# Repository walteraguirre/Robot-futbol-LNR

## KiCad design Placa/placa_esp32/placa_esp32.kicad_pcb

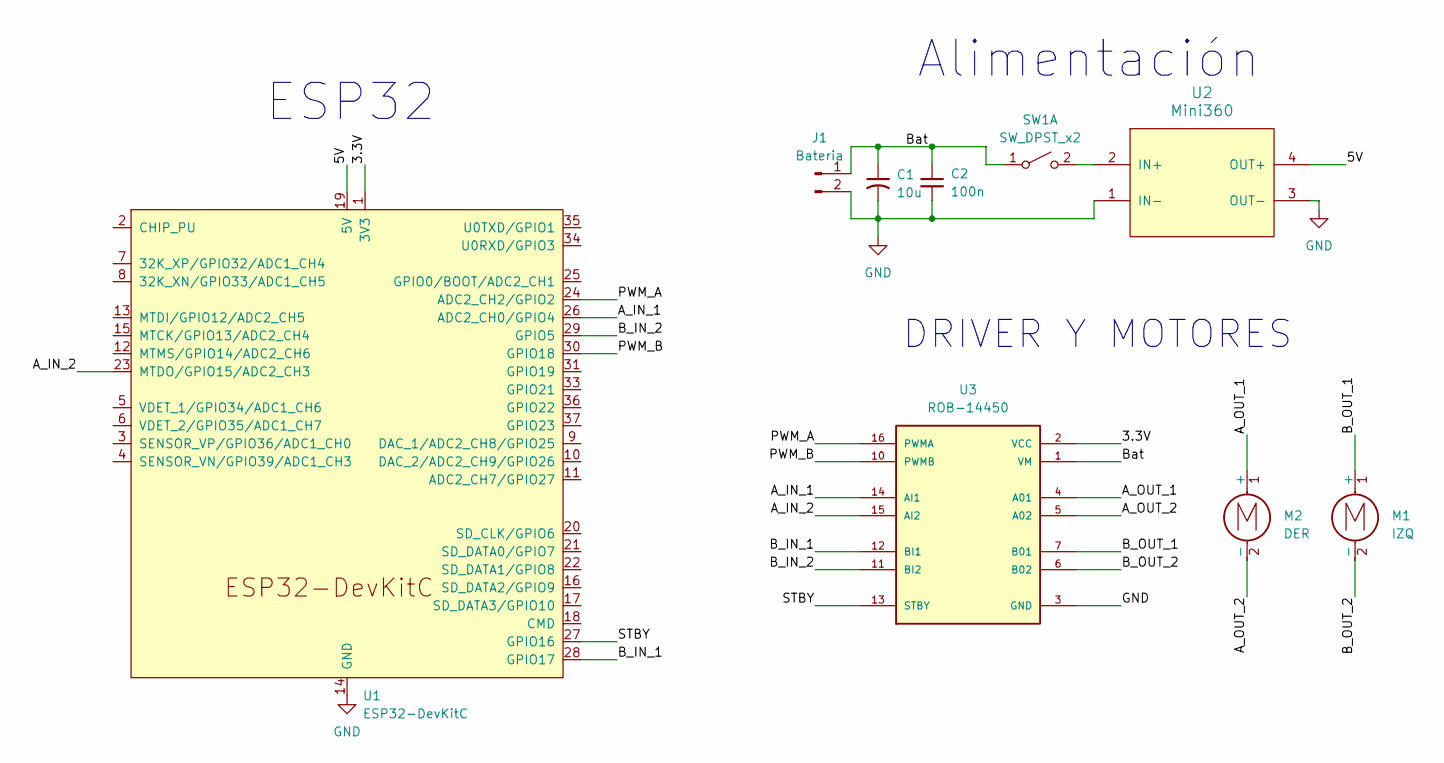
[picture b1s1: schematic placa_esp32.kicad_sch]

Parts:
C1: 10u; C_Radial_D10.0mm_H12.5mm_P5.00mm
C2: 100n; C_Disc_D10.0mm_W2.5mm_P5.00mm
J1: Bateria; JST_EH_B2B-EH-A_1x02_P2.50mm_Vertical
M1: IZQ; JST_EH_B2B-EH-A_1x02_P2.50mm_Vertical
M2: DER; JST_EH_B2B-EH-A_1x02_P2.50mm_Vertical
SW1: SW_DPST_x2; JST_EH_B2B-EH-A_1x02_P2.50mm_Vertical
U1: ESP32-DevKitC
U2: Mini360; Mini360_step-down
U3: ROB-14450; MODULE_ROB-14450; PARTREV 11-13-17

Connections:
/3.3V: U1.1 (3V3), U3.2 (VCC)
/5V: U1.19 (5V), U2.4 (OUT+)
/A_IN_1: U1.26 (ADC2_CH0/GPIO4), U3.14 (AI1)
/A_IN_2: U1.23 (MTDO/GPIO15/ADC2_CH3), U3.15 (AI2)
/A_OUT_1: M2.1 (+), U3.4 (A01)
/A_OUT_2: M2.2 (-), U3.5 (A02)
/B_IN_1: U1.28 (GPIO17), U3.12 (BI1)
/B_IN_2: U1.29 (GPIO5), U3.11 (BI2)
/B_OUT_1: M1.1 (+), U3.7 (B01)
/B_OUT_2: M1.2 (-), U3.6 (B02)
/Bat: C1.1, C2.1, J1.1, SW1.1 (A), U3.1 (VM)
/PWM_A: U1.24 (ADC2_CH2/GPIO2), U3.16 (PWMA)
/PWM_B: U1.30 (GPIO18), U3.10 (PWMB)
/STBY: U1.27 (GPIO16), U3.13 (STBY)
GND: C1.2, C2.2, J1.2, U1.14 (GND), U1.32 (GND), U1.38 (GND), U2.1 (IN-), U2.3 (OUT-), U3.3 (GND), U3.8 (GND), U3.9 (GND)
unnamed: SW1.2 (B), U2.2 (IN+)

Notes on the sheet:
ESP32
Alimentación
DRIVER Y MOTORES

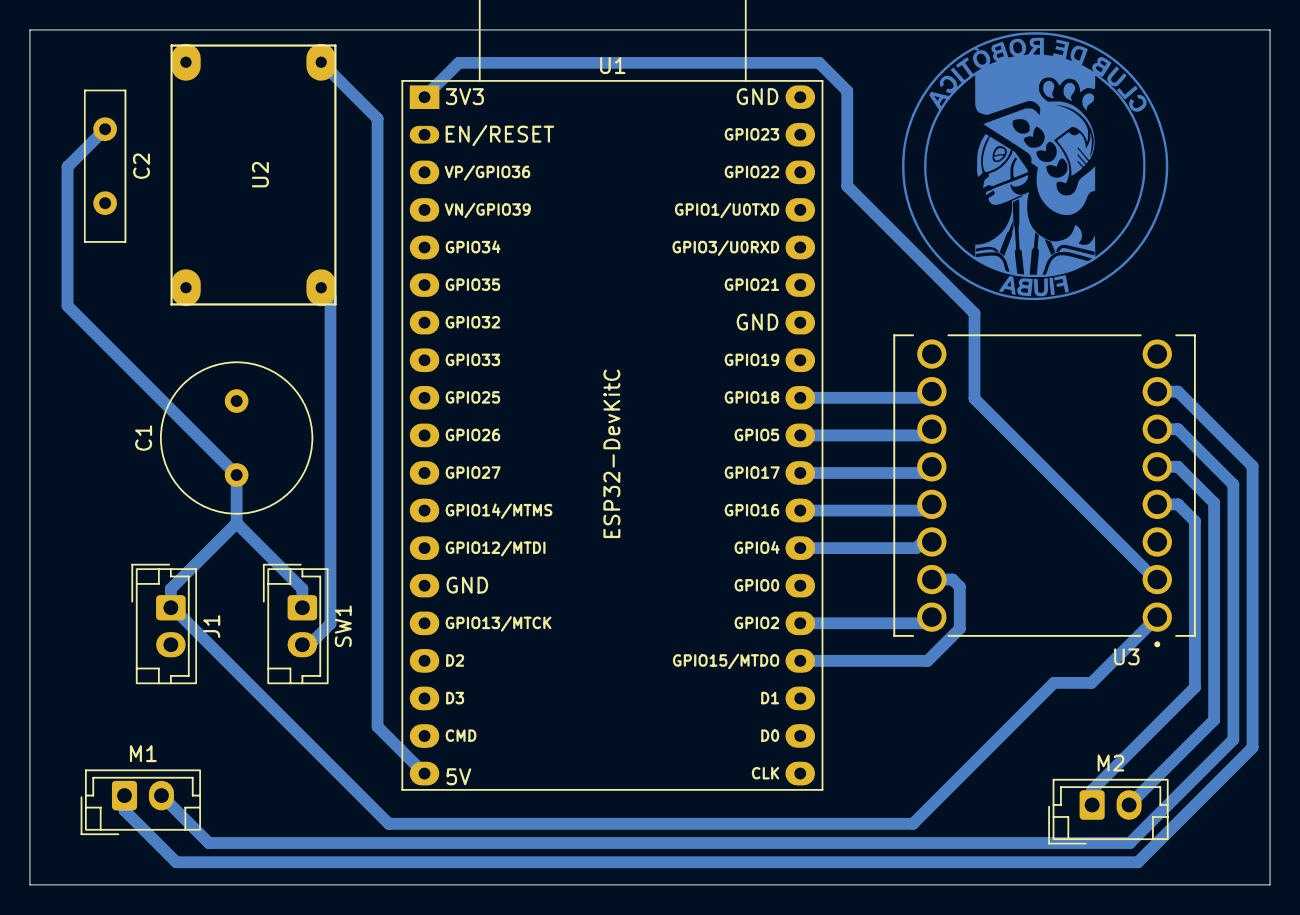
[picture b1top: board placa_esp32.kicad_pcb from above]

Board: 2 copper layers, 83.8 x 57.8 mm, 9 parts (0 on the bottom side), 16 nets.
